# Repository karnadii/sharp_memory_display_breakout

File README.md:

# Sharp Memory Display Breakout (LS011B7DH03)

A breakout board for the Sharp LS011B7DH03, a 1.1-inch, 160x68 pixel monochrome memory display. This display is ideal for low-power applications like wireless keyboards due to its e-paper-like characteristics (~10µA power draw) and high refresh rate (30Hz).

This project is designed to be as small as possible, using fewer components than the Adafruit memory display breakout.

## Versions

This repository contains a few different versions of the breakout board. Production files (Gerber, schematic, STEP) for all versions are available in the [Releases section](https://github.com/karnadii/sharp_memory_display_breakout/releases).

### 1. Original Version (this branch)

This is the original design. It is designed with the pinout of a 128x32 OLED display in mind, making it a potential replacement for common displays used in mechanical keyboards.

### 2. nice!view Compatible Versions

To support the growing ecosystem around the [nice!view](https://nicekeyboards.com/nice-view), compatible versions of this breakout are available. These are intended as a DIY alternative if the nice!view is out of stock. They use the same pinout and should work with the same ZMK configurations.

- **[niceview-compat](https://github.com/karnadii/sharp_memory_display_breakout/tree/niceview-compat)**: Pin-compatible with mounting holes.

- **[niceview-compat-no-mount](https://github.com/karnadii/sharp_memory_display_breakout/tree/niceview-compat-no-mount)**: Pin-compatible without mounting holes for a smaller footprint.

> **Note:** This is a DIY project. For a ready-to-use product, consider purchasing the [nice!view](https://nicekeyboards.com/nice-view) instead.

## Design and Usage

### Pinout Compatibility

The original version is mostly pin-compatible with standard 128x32 I2C OLED displays used in many split keyboards. To replace an OLED, you may need to connect the `CLK` pin to a free GPIO on your microcontroller.

### Installation

The breakout can be used in several ways:
- **Socketed/Soldered:** Solder pin headers to use it directly with a microcontroller board.
- **Daughterboard:** Solder the JST connector and use it as a daughterboard. The mounting holes can be used for this purpose.

If you need a smaller board, the mounting hole tabs can be carefully broken off.

### PCB Size

## Bill of Materials (BOM)

| Ref | Qty | Value | Footprint | LCSC Part # | Notes |
|:--- |:---:|:------|:----------|:------------|:------|
| C1 | 1 | 560pF or 680pF | 0603 | C84721 | Unpolarized Capacitor |
| C2,C3 | 2 | 1uF | 0603 | C15849 | Unpolarized Capacitor |
| FB1,FB2 | 2 | Ferrite Bead | 0805 | C1017 | |
| J2 | 1 | FH12-10S-0.5SH | - | C506791 | FPC Connector |
| J3 | 1 | JST SH 5x1 | - | [AliExpress](https://www.aliexpress.com/item/1005003131441676.html) | Optional |
| R1,R2,R3 | 3 | 10kΩ | 0603 | C25804 | Optional |
| Display | 1 | LS011B7DH03 | - | [AliExpress](https://aliexpress.com/item/1005001809102193.html) | |

**Notes:**
- The resistors (R1, R2, R3) are optional and may not be required for the display to function.
- The LS011B7DH03 display can be difficult to source. The link provided is one of the few known sellers on AliExpress. Quality may vary.

## Cost Estimate

This is a DIY project. The approximate cost for a single breakout board is **$15 - $20** (before shipping), assuming you order 5 PCBs from a service like JLCPCB and source the displays from AliExpress. Costs can be reduced by sourcing components from cheaper vendors and self-assembly.

For comparison, the pre-built [nice!view](https://nicekeyboards.com/nice-view) is sold for around $20.

## Demos

The breakout has been tested with CircuitPython, Arduino, and ZMK (on an nrfmicro). Example code can be found in the `test_code` folder.

### Arduino
https://user-images.githubusercontent.com/18657277/137644641-276d998f-445c-41ad-aaf1-b85f445b7fb1.mp4

### CircuitPython
https://user-images.githubusercontent.com/18657277/146429499-8556456f-ffeb-47a3-a99c-73e11da73714.mp4

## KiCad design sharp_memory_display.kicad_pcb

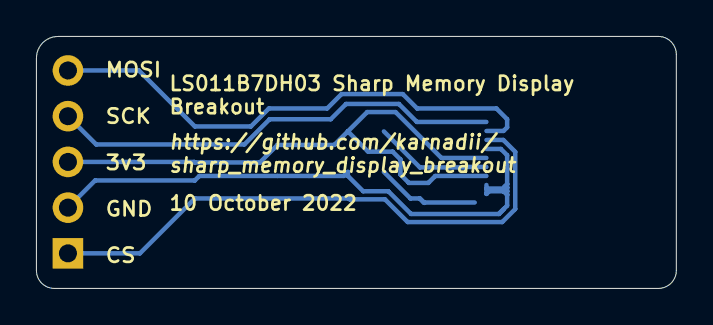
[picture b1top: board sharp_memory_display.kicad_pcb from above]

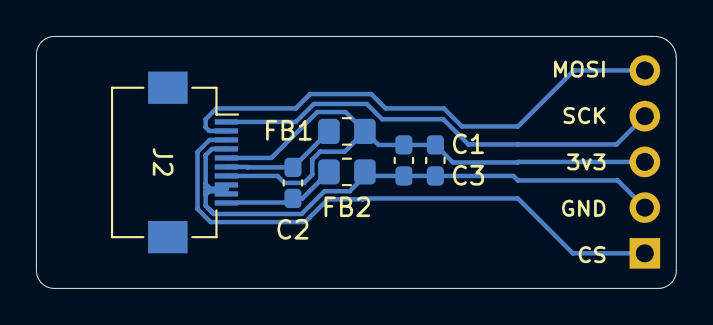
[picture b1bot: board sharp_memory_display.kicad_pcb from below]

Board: 2 copper layers, 35.5 x 14.0 mm, 7 parts (6 on the bottom side), 7 nets.

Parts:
C1: 560pF/680pF; C_0603_1608Metric_Pad1.08x0.95mm_HandSolder
C2, C3: 1uF; C_0603_1608Metric_Pad1.08x0.95mm_HandSolder
FB1, FB2: Ferrite_Bead_Small; R_0805_2012Metric_Pad1.20x1.40mm_HandSolder
J1: Conn_01x05; PinSocket_1x05_P2.54mm_Vertical
J2: Conn_01x10; Hirose_FH12-10S-0.5SH_1x10-1MP_P0.50mm_Horizontal

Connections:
DISP: C1.1, C3.1, FB1.2, J1.3, J2.5, J2.7
EXTCOMIN: C1.2, C3.2, FB2.1, J1.2, J2.4, J2.8, J2.9
SCLK: J1.4, J2.1
SCS: J1.1, J2.3
SI: J1.5, J2.2
VDDA: C2.1, FB1.1, J2.6
VSSA: C2.2, FB2.2, J2.10

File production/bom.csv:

Designator,Footprint,Quantity,Value,LCSC Part #
C1,C_0603_1608Metric_Pad1.08x0.95mm_HandSolder,1,560pF/680pF,C84721
C2,C_0603_1608Metric_Pad1.08x0.95mm_HandSolder,1,1uF,C15849
C3,C_0603_1608Metric_Pad1.08x0.95mm_HandSolder,1,1uF ,C15849
"FB1, FB2",R_0805_2012Metric_Pad1.20x1.40mm_HandSolder,2,Ferrite_Bead_Small,C1017
J1,PinSocket_1x05_P2.54mm_Vertical,1,Conn_01x05,
J2,Hirose_FH12-10S-0.5SH_1x10-1MP_P0.50mm_Horizontal,1,Conn_01x10,C506791

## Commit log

2021-09-16 add solderable pad
2022-03-16 add pullup resistor for DISP
2022-08-05 add new BOM and IBOM
2022-08-05 update readme and arduino code
2022-08-14 add test code for circuitpython
2022-08-17 tidy up schematic
2022-08-27 add 3d files and update readme
2022-09-18 update on ZMK
2022-10-10 nice!view compatible
2022-10-10 no mounting holes version
2023-10-27 Create LICENSE
2025-06-28 docs: Tidy up README.md
2025-06-28 docs: Remove ZMK line and ™ from README.md
2025-06-28 docs: Remove ZMK section from README.md
2025-06-28 docs: Change license to CERN-OHL-P-2.0
2025-06-28 chore: Remove old backup files
2025-06-28 style: Improve formatting of LICENSE file
2025-06-28 Remove outdated backup zip files from sharp_memory_display-backups directory
